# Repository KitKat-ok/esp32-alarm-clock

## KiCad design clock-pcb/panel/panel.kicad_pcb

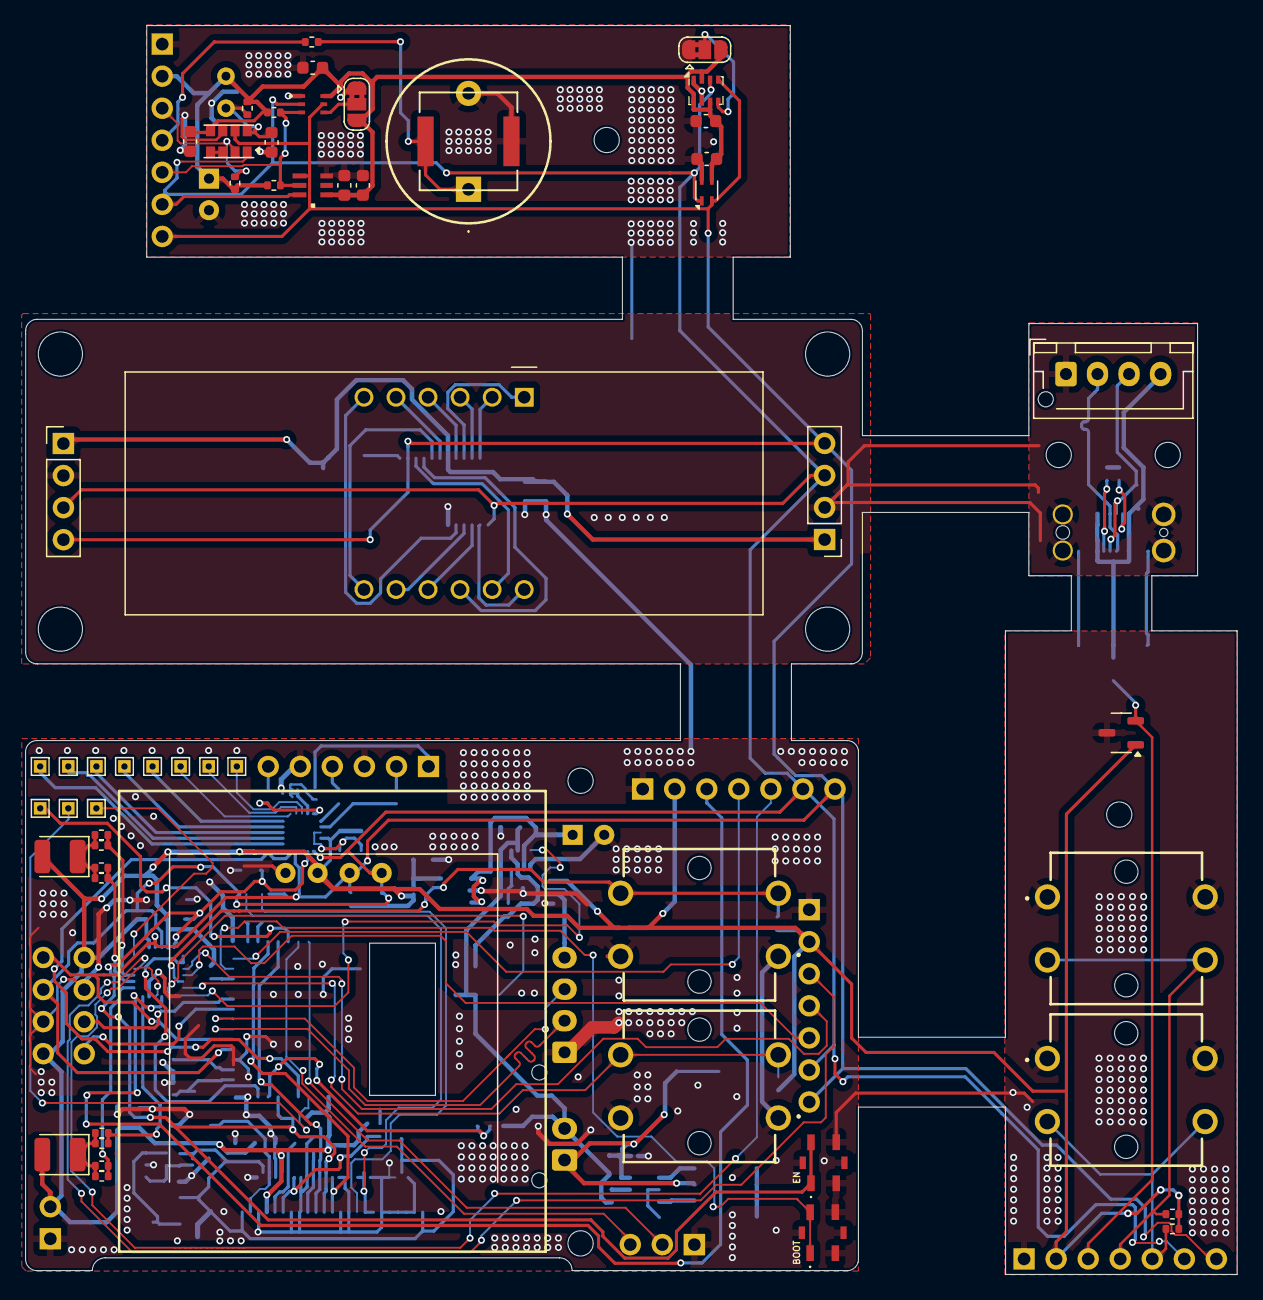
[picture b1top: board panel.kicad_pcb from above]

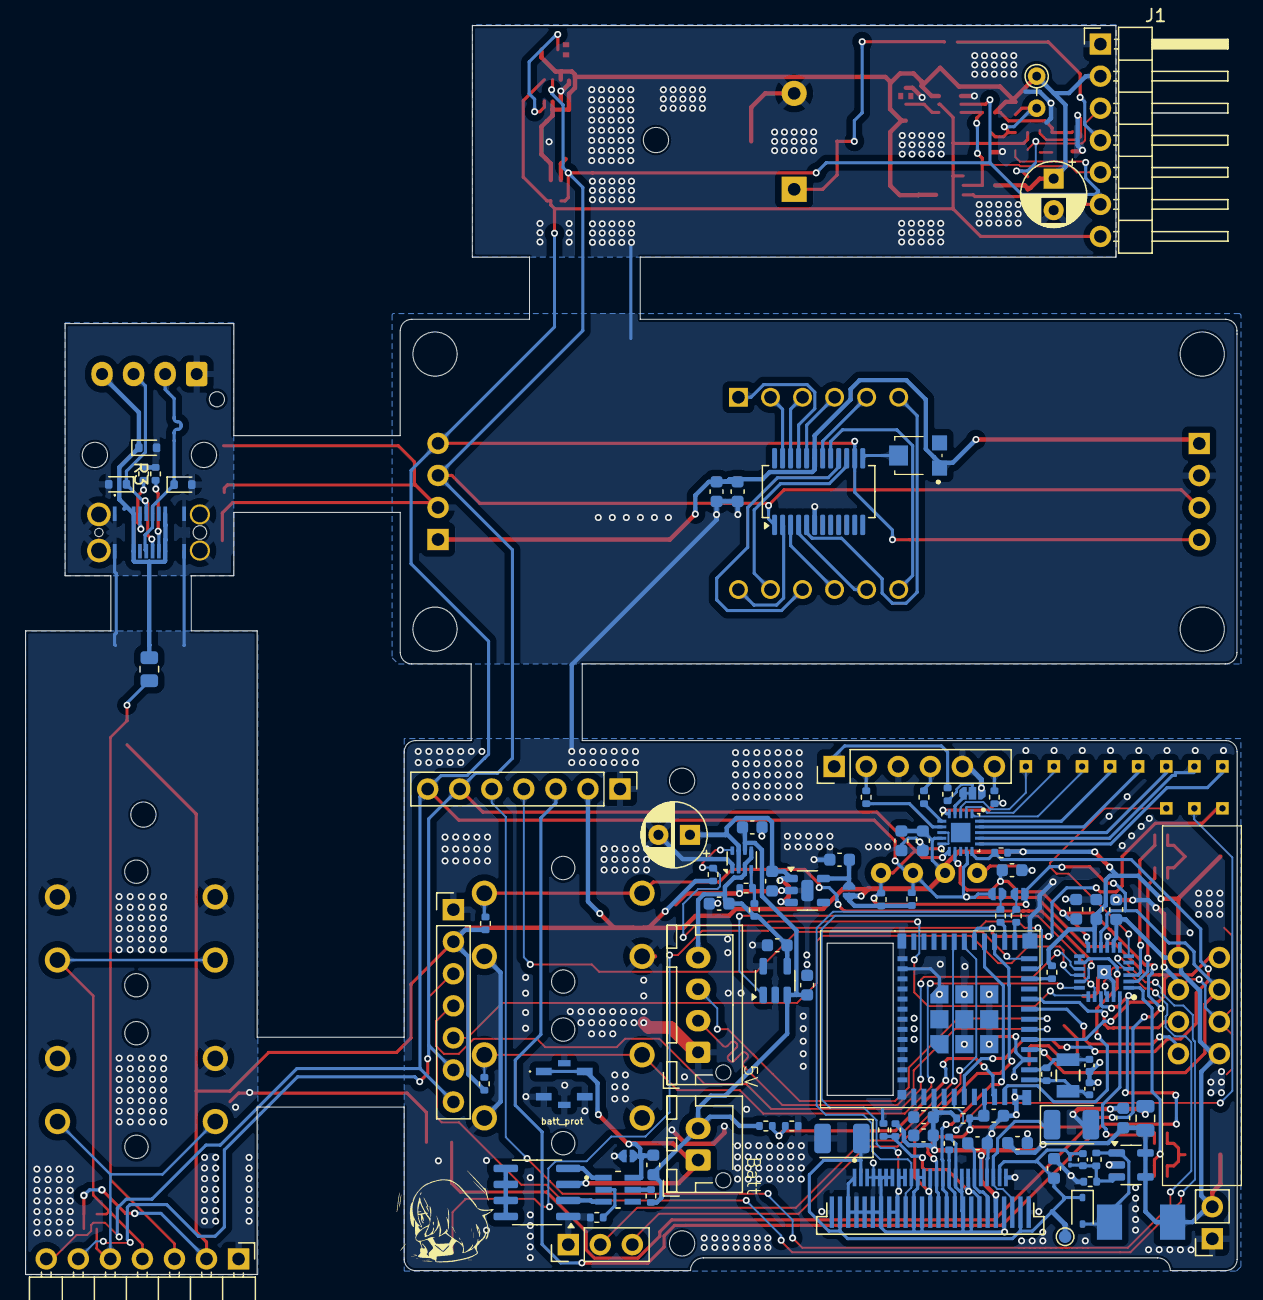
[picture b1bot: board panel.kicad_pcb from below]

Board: 2 copper layers, 96.0 x 99.0 mm, 154 parts (95 on the bottom side), 98 nets.

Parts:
AO9926C1: SOIC-8_3.9x4.9mm_P1.27mm
C1, C1#2, C2, C2#2, C3, C4#2, C6, C23, C23#2: 0.1uF; C_0603_1608Metric
C3#2, C17, C24, C24#2: 10uF; C_0603_1608Metric
C4: 4.7uF; C_0603_1608Metric
C5, C6#2, C7, C8, C9, C10, C11, C12, C13, C13#2, C14, C15, C21, C25, C28: 1uF; C_0603_1608Metric
C5#2, C7#2: 100uF; CP_Radial_D5.0mm_P2.50mm
C16: 4.7uF; C_0805_2012Metric
C18: 6.4pF; C_0402_1005Metric
C19, C20: 19pF; C_0402_1005Metric
C22: 6.4pF; C_01005_0402Metric
C26, C27: 4.7uF; CP_EIA-3528-12_Kemet-T
D1, D2: LED; LED_1210_3225Metric
D1#2, D2#2, D3#2: ESD5Zxx; D_SOD-523
D3: NSVR0340HT1G; D_SOD-323
IC1: VEML6030-GS15; VEML6030GS15
IC2: MCP23018-E_MJ; QFN50P400X400X90-25N-D
J1, J2: Conn_01x04_Socket; PinHeader_1x04_P2.54mm_Vertical
J1#2, J1#3: Conn_01x07_Socket; PinHeader_1x07_P2.54mm_Horizontal
J1#4: Conn_01x03_Pin; PinHeader_1x03_P2.54mm_Vertical
J1#5: USB4145-03-0070-C; USB4145030070C
J2#2: oled 2; SSD1306_0.96_Oled
J3: Led display; tm1637_module
J4: Led display 2; PinHeader_1x04_P2.54mm_Vertical
J5, J6: Conn_01x07_Socket; PinHeader_1x07_P2.54mm_Vertical
J7: SFV25R-2STE1HLF; OLED_1.5IN_128X128MONO
J8, J9: Conn_01x04_Socket; JST_XH_B4B-XH-AM_1x04_P2.50mm_Vertical
J8#2: SFV25R-2STE1HLF; AMPHENOL_SFV25R-2STE1HLF
J11: Conn_01x06_Socket; PinHeader_1x06_P2.54mm_Vertical
J15: Conn_01x02_Socket; PinSocket_1x02_P2.54mm_Vertical
JP1, JP2: SolderJumper_3_Bridged12; SolderJumper-3_P1.3mm_Bridged2Bar12_RoundedPad1.0x1.5mm
JP1#2, JP5, JP6, JP7: Jumper; jumper_solder_small
JP2#2: SolderJumper_3_Bridged12; jumper_solder_small_3_bridged
L1: CPT-14146-80T; CPT1414680T
L1#2: 10uH 1A; HPI0530-100
LS1: Speaker_Crystal; AST0760_MAL
R0, R1#4, R3#2: 5.1k; R_0402_1005Metric
R1, R1#2, R2, R3, R6, R8, R9, R10, R11, R11#2, R15, R16, R28, R30, R31: 10K; R_0402_1005Metric
R1#3, R12, R14: 100k; R_0402_1005Metric
R2#2, R26: 300k; R_0402_1005Metric
R3#3: 800k; R_0402_1005Metric
R4, R4#2: 330R; R_0402_1005Metric
R5: 22R; R_0402_1005Metric
R5#2: 2.7K; R_0402_1005Metric
R6#2: 22R; R_Axial_DIN0204_L3.6mm_D1.6mm_P2.54mm_Vertical
R7: 47K; R_0402_1005Metric
R13: 250k; R_0402_1005Metric
R17, R18, R19, R20, R22, R23, R24, R25: 330; R_0402_1005Metric
R21: 10M; R_0402_1005Metric
R27: 3.16M; R_0402_1005Metric
R29: 1.2M; R_0402_1005Metric
R32, R33: N/A; R_0402_1005Metric
S1, S2, S3, S4: B3F-5050; B3F-4055
S1#2, S2#2, S5: TS21-34-035-BK-160-SMT-TR; TS2134035BK160SMTTR
TP1, TP3, TP4, TP5, TP6, TP7, TP8, TP9, TP10, TP12, TP13: TestPoint; TestPoint_THTPad_1.0x1.0mm_Drill0.5mm
TP2: TestPoint; TestPoint_Pad_D1.0mm
U1: BMP280; Bosch_LGA-8_2x2.5mm_P0.65mm_ClockwisePinNumbering
U1#2: CC56-12EWA; CA56-12EWA
U1#3: TMAG5231C1GQDBZR; SOT-23-3
U1#4: ESP32-C6-MINI-1-N4; XCVR_ESP32-C6-MINI-1-N4
U2: LTR-F216A
U2#2: AS1115-BSST; QSOP-24_3.9x8.7mm_P0.635mm
U2#3: SOT95P280X140-6N
U3: APDS-9960; Avago_APDS-9960
U3#2: JST_XH_B2B-XH-AM_1x02_P2.50mm_Vertical
U4: SHT4x; Sensirion_DFN-4_1.5x1.5mm_P0.8mm_SHT4x_NoCentralPad
U4#2: TPS2116DRL; SOT-583-8
U5: MCP73811T-420I-OT; SOT-23-5
U6: TPS61040DBV; SOT-23-5
U7: TLV75533PDBV; TLV75733PDYDR
U8: AT42QT2120-MMHR; QFN45P300X300X85-21N
VR1: TC33X-2-303E; TC33X2304E
Y2: 32.768KHz; XTAL_9HT10_TXC

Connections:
14V_OLED: C17.1, C18.1, C22.1, C27.1, D3.1 (K), J7.2, J7.24, J8#2.2, J8#2.24, TP2.1
+3.3V: C23.1, C24#2.1, J1.1, J2.1, U2#2.19 (VDD), VR1.1 (CCW)
+3V3: C1.2, C1#2.2, C2.2, C2#2.1, C3.1, C3#2.1, C4.1, C6.2, C7#2.1, C13.1, C15.2, C16.1, C21.2, C23#2.1, C24.1, C28.2, D1.2 (A), D2.2 (A), IC1.6 (VDD), IC2.8 (VDD), IC2.11 (ADDR), J1#2.2, J1#3.2, J2#2.2, J3.4, J4.4, J5.2, J6.2, J7.5, J8#2.21, J15.2, JP1.3 (B), JP2.3 (B), JP7.2 (B), L1#2.2, R0.1, R1.2, R1#2.1, R1#3.1, R2.1, R3.1, R5.1, R6.2, R6#2.1, R7.1, R11.2, R11#2.1, R12.1, R15.2, R28.2, R31.1, U1.2 (CSB), U1.6 (VDDIO), U1.8 (VDD), U1#3.1 (VCC), U1#4.3 (3V3), U2.1 (VDD), U3.5 (LED_A), U4.3 (VDD), U6.4 (EN), U6.5 (VIN), U8.9 (VDD)
+BATT: C4#2.2, C7.1, C11.1, R2#2.1, R4#2.2, U3#2.2, U4#2.6 (VIN2), U5.3 (V_{BAT})
-BATT: AO9926C1.3 (S1), C4#2.1, JP1#2.1 (A), S5.1 (COM_1), S5.2 (COM_2), U2#3.6 (VSS), U3#2.1
ADC: R2#2.2, R3#3.1, U1#4.9 (IO4)
BUTON_CONF: IC2.16 (GPA1), J1#3.5, J6.5, R11.1, S1.3 (NO_1), S1.4 (NO_2)
BUTTON_DOWN: IC2.18 (GPA3), R28.1, S4.3 (NO_1), S4.4 (NO_2)
BUTTON_EXIT: IC2.15 (GPA0), J1#3.4, J6.4, R1.1, S2.3 (NO_1), S2.4 (NO_2)
BUTTON_UP: IC2.17 (GPA2), R15.1, S3.3 (NO_1), S3.4 (NO_2)
BUZZER: J1#2.4, J5.4, R4.2, U1#4.24 (IO18)
BUZZER_IN: L1.1, LS1.1, R4.1
CHARGE_EN: IC2.20 (GPA5), U5.1 (CE)
CLK: J4.1, U1#4.19 (IO14)
CLOCK_N: C19.1, R21.1, U1#4.13 (IO1), Y2.1
CLOCK_P: C20.1, R21.2, U1#4.12 (IO0), Y2.2
CS: J7.11, J8#2.15, U1#4.28 (IO22)
DC: J7.13, J8#2.13, U1#4.27 (IO21)
DIGIT-1: U1#2.12 (CC1), U2#2.2 (DIG0)
DIGIT-2: U1#2.9 (CC2), U2#2.3 (DIG1)
DIGIT-3: U1#2.8 (CC3), U2#2.4 (DIG2)
DIGIT-4: U1#2.6 (CC4), U2#2.5 (DIG3)
DIO: J4.2, U1#4.20 (IO15)
DN: D2#2.1 (K), J1#5.A7 (DN1), J1#5.B7 (DN2), J8.2, J9.2, U1#4.17 (IO12)
DP: D3#2.1 (K), J1#5.A6 (DP1), J1#5.B6 (DP2), J8.3, J9.3, U1#4.18 (IO13)
EN: C12.2, C13#2.1, C14.2, IC2.12 (~RESET), J7.12, J8#2.14, R11#2.2, S2#2.1 (COM_1), S2#2.2 (COM_2), U1#4.8 (EN), U8.12 (~RESET)
GND: AO9926C1.1 (S2), C1.1, C1#2.1, C2.1, C2#2.2, C3.2, C3#2.2, C4.2, C5.2, C5#2.2, C6.1, C6#2.1, C7.2, C7#2.2, C8.2, C9.2, C10.2, C11.2, C12.1, C13.2, C13#2.2, C14.1, C15.1, C16.2, C17.2, C19.2, C20.2, C21.1, C23.2, C23#2.2, C24.2, C24#2.2, C25.1, C26.2, C27.2, C28.1, D1#2.2 (A), D2#2.2 (A), D3#2.2 (A), IC1.1 (GND), IC2.23 (VSS), IC2.25 (EP), J1.2, J1#2.1, J1#3.1, J1#4.1, J1#5.A1 (GND_1), J1#5.A12 (GND_2), J1#5.B1 (GND_3), J1#5.B12 (GND_4), J1#5.MH1, J1#5.MH2, J1#5.MH3, J1#5.MH4, J2.2, J2#2.1, J3.3, J4.3, J5.1, J6.1, J7.1, J7.4, J7.8, J7.9, J7.14, J7.15, J7.19, J7.20, J7.21, J7.22, J7.23, J7.25, J8.1, J8#2.1, J8#2.3, J8#2.4, J8#2.5, J8#2.6, J8#2.7, J8#2.11, J8#2.12, J8#2.17, J8#2.18, J8#2.22, J8#2.25, J9.1, J11.3, J11.5, J15.1, JP1.1 (A), JP1#2.2 (B), JP2.1 (A), JP2#2.3 (B), L1.2, LS1.2, R1#4.2, R3#2.2, R3#3.2, R5#2.2, R14.1, R26.2, R29.2, R30.1, S1.1 (COM_1), S1.2 (COM_2), S1#2.3 (NO_1), S1#2.4 (NO_2), S1#2.MP1, S1#2.MP2, S2.1 (COM_1), S2.2 (COM_2), S2#2.3 (NO_1), S2#2.4 (NO_2), S2#2.MP1, S2#2.MP2, S3.1 (COM_1), S3.2 (COM_2), S4.1 (COM_1), S4.2 (COM_2), S5.3 (NO_1), S5.4 (NO_2), S5.MP1, S5.MP2, U1.1 (GND), U1.7 (GND), U1#3.3 (GND), U1#4.1 (GND1), U1#4.2 (GND1__1), U1#4.11 (GND1__2), U1#4.14 (GND1__3), U1#4.36 (GND1__4), U1#4.37 (GND1__5), U1#4.38 (GND1__6), U1#4.39 (GND1__7), U1#4.40 (GND1__8), U1#4.41 (GND1__9), U1#4.42 (GND1__10), U1#4.43 (GND1__11), U1#4.44 (GND1__12), U1#4.45 (GND1__13), U1#4.46 (GND1__14), U1#4.47 (GND2), U1#4.48 (GND2__1), U1#4.49_1 (GND2__2), U1#4.49_2 (GND2__3), U1#4.49_3 (GND2__4), U1#4.49_4 (GND2__5), U1#4.49_5 (GND2__6), U1#4.49_6 (GND2__7), U1#4.49_7 (GND2__8), U1#4.49_8 (GND2__9), U1#4.49_9 (GND2__10), U1#4.50 (GND2__11), U1#4.51 (GND2__12), U1#4.52 (GND2__13), U1#4.53 (GND2__14), U2.3 (GND), U2#2.6 (GND), U3.6 (GND), U4.4 (VSS), U4#2.1 (GND), U5.2 (V_{SS}), U5.5 (PROG), U6.2 (GND), U7.2 (GND), U8.8 (VSS), U8.10 (MODE)
GPIO9: S1#2.1 (COM_1), S1#2.2 (COM_2), U1#4.23 (IO9)
GUARD: JP2#2.1 (A), JP2#2.2 (C), R9.2, U8.4 (KEY3/GPO1)
HALL_SENS: IC2.4 (GPB4), J1#3.3, J6.3, U1#3.2 (OUT)
INT_A: IC2.13 (INTB), IC2.14 (INTA), U1#4.10 (IO5)
LDO_IN: C5#2.1, C9.1, U4#2.2 (VOUT), U4#2.7 (VOUT), U7.1 (IN), U7.3 (EN)
LED1_P1: IC2.24 (GPB0), R17.1, R19.1
LED1_P2: IC2.1 (GPB1), R18.1, R20.1
LED2_P1: IC2.2 (GPB2), R22.1, R23.1
LED2_P2: IC2.3 (GPB3), R24.1, R25.1
MOSI: J7.17, J7.18, J8#2.8, J8#2.9, JP5.2 (B), R33.1
unnamed: AO9926C1.5 (D1), AO9926C1.6 (D1), AO9926C1.7 (D2), AO9926C1.8 (D2)
unnamed: AO9926C1.4 (G1), U2#3.1 (DO)
unnamed: AO9926C1.2 (G2), U2#3.3 (CO)
unnamed: C25.2, J7.6, J8#2.20
unnamed: C26.1, J7.3, J8#2.23
unnamed: D1.1 (K), R17.2, R18.2, R19.2, R20.2
unnamed: D2.1 (K), R22.2, R23.2, R24.2, R25.2
unnamed: D3.2 (A), L1#2.1, R27.1, U6.1 (SW)
unnamed: IC1.4 (ADDR), JP1.2 (C)
unnamed: IC2.6 (GPB6), TP10.1
unnamed: J1#5.A5 (CC1), R1#4.1
unnamed: J1#5.B5 (CC2), R3#2.1
unnamed: J7.7, J8#2.19, R30.2, R31.2
unnamed: J7.10, J8#2.16, R29.1
unnamed: J11.1, R9.1
unnamed: J11.2, R16.1
unnamed: J11.4, R10.1
unnamed: J11.6, R8.1
unnamed: JP2.2 (C), U1.5 (SDO)
unnamed: C8.1, JP7.1 (A), U7.5 (OUT)
unnamed: U1#2.3 (DPX), U2#2.22 (SEGDP)
unnamed: TP9.1, U1#4.5 (IO2)
unnamed: R0.2, U1#4.22 (IO8)
unnamed: R33.2, U1#4.25 (IO19)
unnamed: R32.2, U1#4.26 (IO20)
unnamed: TP1.1, U1#4.29 (IO23)
unnamed: U1#2.11 (a), U2#2.15 (SEGA)
unnamed: U1#2.7 (b), U2#2.17 (SEGB)
unnamed: U1#2.4 (c), U2#2.20 (SEGC)
unnamed: U1#2.2 (d), U2#2.23 (SEGD)
unnamed: U1#2.1 (e), U2#2.21 (SEGE)
unnamed: U1#2.10 (f), U2#2.16 (SEGF)
unnamed: U1#2.5 (g), U2#2.18 (SEGG)
unnamed: U2#2.13 (ISET), VR1.2 (WIPER)
unnamed: R4#2.1, U2#3.5 (VDD)
unnamed: R5#2.1, U2#3.2 (VM)
unnamed: U3.3 (LDR), U3.4 (LED_K)
unnamed: C5.1, R5.2, R6#2.2, U3.8 (VDD)
unnamed: R13.1, R14.2, U4#2.4 (PR1)
unnamed: C18.2, C22.2, R26.1, R27.2, U6.3 (FB)
unnamed: TP13.1, U8.3 (KEY4/GPO2)
unnamed: TP12.1, U8.2 (KEY5/GPO3)
unnamed: TP8.1, U8.1 (KEY6/GPO4)
unnamed: TP7.1, U8.20 (KEY7/GPO5)
unnamed: TP6.1, U8.19 (KEY8/GPO6)
unnamed: TP5.1, U8.18 (KEY9/GPO7)
unnamed: TP4.1, U8.17 (KEY10/GPO8)
unnamed: TP3.1, U8.16 (KEY11/GPO9)
POWER_STATUS: IC2.19 (GPA4), R6.1, U4#2.8 (ST)
RX: J1#4.3, U1#4.30 (RXD0)
SCL: IC1.5 (SCL), IC2.9 (SCL), J1.4, J1#2.7, J1#3.7, J2.4, J2#2.3, J3.1, J5.7, J6.7, JP6.1 (A), R1#3.2, U1.4 (SCK), U1#4.16 (IO7), U2.4 (SCL), U2#2.14 (SCL), U3.7 (SCL), U4.2 (SCL), U8.14 (SCL)
SCLK: J7.16, J8#2.10, JP6.2 (B), R32.1
SDA: IC1.2 (SDA), IC2.10 (SDA), J1.3, J1#2.6, J1#3.6, J2.3, J2#2.4, J3.2, J5.6, J6.6, JP5.1 (A), R12.2, U1.3 (SDI), U1#4.15 (IO6), U2.6 (SDA), U2#2.1 (SDA), U3.1 (SDA), U4.1 (SDA), U8.11 (SDA)
SLID_0: R16.2, U8.7 (KEY0)
SLID_1: R10.2, U8.6 (KEY1)
SLID_2: R8.2, U8.5 (KEY2/GPO0)
SUB_TOP_1: IC1.3 (INT), IC2.22 (GPA7), J1#2.5, J5.5, R1#2.2, R2.2, U2.5 (INT)
SUB_TOP_3: IC2.21 (GPA6), J1#2.3, J5.3, R3.2, U3.2 (INT)
TOUCH_INT: R7.2, U1#4.6 (IO3), U8.15 (~CHANGE)
TX: J1#4.2, U1#4.31 (TXD0)
VBUS: C6#2.2, C10.1, D1#2.1 (K), J1#5.A4 (VBUS_1), J1#5.A9 (VBUS_2), J1#5.B4 (VBUS_3), J1#5.B9 (VBUS_4), J8.4, J9.4, R13.2, U4#2.3 (VIN1), U4#2.5 (MODE), U5.4 (V_{DD})
